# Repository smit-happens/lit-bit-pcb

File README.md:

# lit-bit-pcb
For the embedded systems lit-bit project

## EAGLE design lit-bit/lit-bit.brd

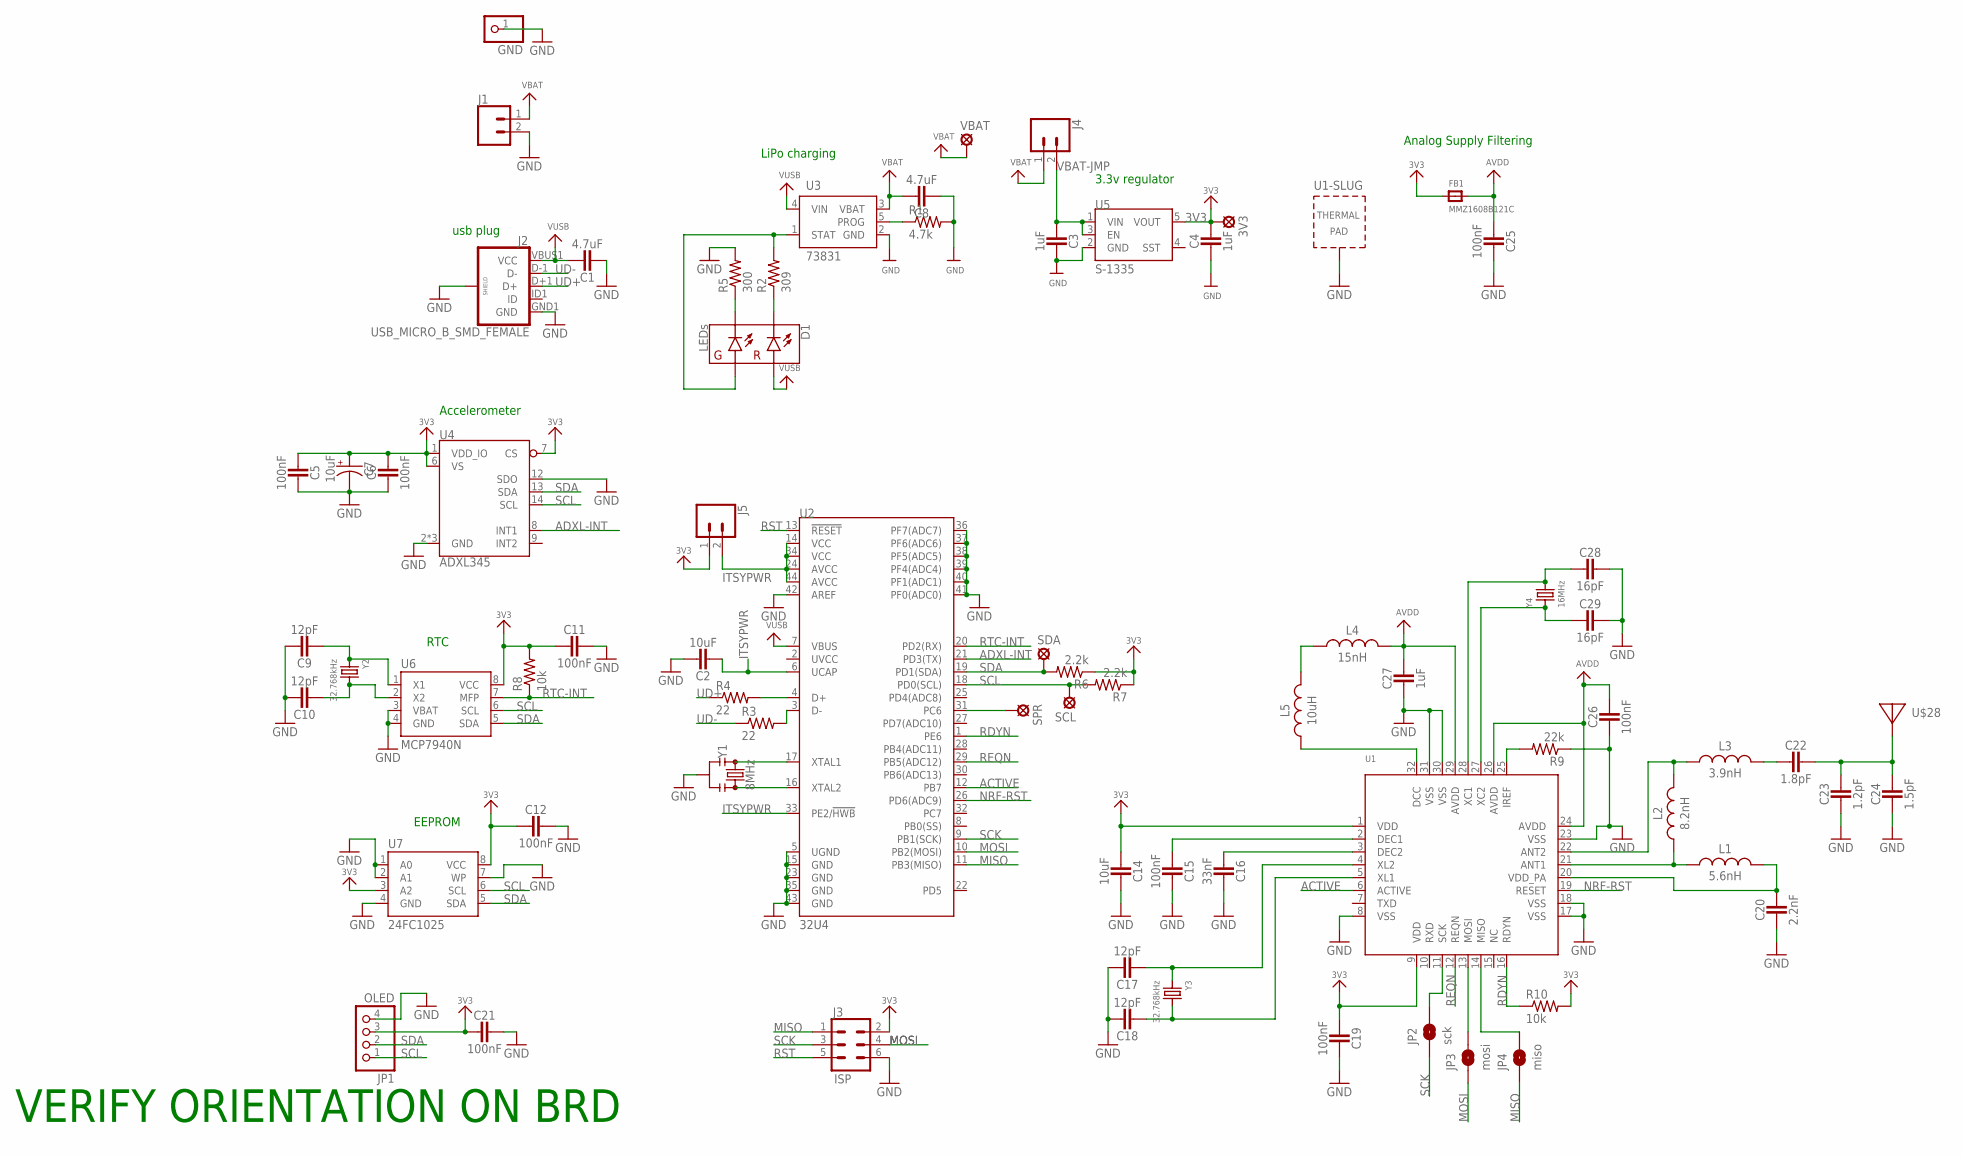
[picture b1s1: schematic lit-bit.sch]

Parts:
3V3: LSP10
C1, C8: 4.7uF; 0603
C2, C14: 10uF; 0603
C3, C4, C27: 1uF; 0603
C5, C6, C11, C12, C15, C19, C21, C25, C26: 100nF; 0603
C7: 10uF; 0805-POLAR
C9, C10, C17, C18: 12pF; 0603
C16: 33nF; 0603
C20: 2.2nF; 0603
C22: 1.8pF; 0603
C23: 1.2pF; 0603
C24: 1.5pF; 0603
C28, C29: 16pF; 0603
D1: LEDs; 0606
FB1: MMZ1608B121C; 0805
GND: HEADER-1X1ROUND; 1X01_ROUND
J1: CONN_02-JST-2MM-SMT; JST-2-SMD
J2: USB_MICRO_B_SMD_FEMALE; USB-B-MICRO-SMD
J3: ISP; 2X3
J4, J5: CONN_02; 1X02
JP1: OLED; 1X04_ROUND
JP2: sck; SMT-JUMPER_2_NO_SILK
JP3: mosi; SMT-JUMPER_2_NO_SILK
JP4: miso; SMT-JUMPER_2_NO_SILK
L1: 5.6nH; 0603
L2: 8.2nH; 0603
L3: 3.9nH; 0603
L4: 15nH; 0603
L5: 10uH; 0603
R1: 4.7k; 0603
R2: 309; 0603
R3, R4: 22; 0603
R5: 300; 0603
R6, R7: 2.2k; 0603
R8, R10: 10k; 0603
R9: 22k; 0603
SCL: LSP10
SDA: LSP10
SPR: LSP10
U1: NRF8001; QFN32_5MM
U2: 32U4; TQFP44
U3: 73831; SOT23-5
U4: ADXL345; LGA-14
U5: S-1335; SOT23-5
U6: MCP7940N; 8-SOIC_HAND_SOLDER
U7: 24FC1025; 8-SOIC_HAND_SOLDER
U$28: ANTENNA_PCBNRF8001_1.6MM; ANT_PCB_2.4GHZ_NRF8001_1.6MM_1OZ
VBAT: LSP10
Y1: 8MHz; RESONATOR-SMD-3.2X1.3
Y2, Y3: 32.768kHz; CRYSTAL_8X3.8
Y4: 16MHz; CRYSTAL_3.2X2.5

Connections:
3V3: 3V3.MP, C4.1, C5.2, C6.1, C7.1 (+), C11.2, C12.2, C14.2, C19.2, C21.2, FB1.1, J3.2, J5.1, JP1.3, R6.1, R7.1, R8.2, R10.2, U1.1 (VDD), U1.9 (VDD), U4.1 (VDD_IO), U4.6 (VS), U4.7 (CS), U5.5 (VOUT), U6.8 (VCC), U7.3 (A2), U7.8 (VCC)
ACTIVE: U1.6 (ACTIVE), U2.12 (PB7)
ADXL-INT: U2.21 (PD3(TX)), U4.8 (INT1)
AVDD: C25.2, C26.1, C27.1, FB1.2, L4.2, U1.24 (AVDD), U1.26 (AVDD), U1.29 (AVDD)
D+: R4.2, U2.4 (D+)
GND: C1.2, C2.1, C3.1, C4.2, C5.1, C6.2, C7.2 (-), C8.2, C9.1, C10.1, C11.1, C12.1, C14.1, C15.1, C16.1, C17.1, C18.1, C19.1, C20.2, C21.1, C23.2, C24.2, C25.1, C26.2, C27.2, C28.1, C29.1, GND.1, J1.2 (1), J2.GND1 (GND), J2.P$1 (SHIELD), J2.P$3 (SHIELD), J2.P$4 (SHIELD), J2.P$5 (SHIELD), J3.6, JP1.4, R1.2, R5.2, R9.1, U1.8 (VSS), U1.17 (VSS), U1.18 (VSS), U1.23 (VSS), U1.30 (VSS), U1.31 (VSS), U1.33 (TP), U2.5 (UGND), U2.15 (GND), U2.23 (GND), U2.35 (GND), U2.36 (PF7(ADC7)), U2.37 (PF6(ADC6)), U2.38 (PF5(ADC5)), U2.39 (PF4(ADC4)), U2.40 (PF1(ADC1)), U2.41 (PF0(ADC0)), U2.42 (AREF), U2.43 (GND), U3.2 (GND), U4.2 (GND), U4.4 (GND), U4.5 (GND), U4.12 (SDO), U5.2 (GND), U6.3 (VBAT), U6.4 (GND), U7.1 (A0), U7.2 (A1), U7.4 (GND), U7.7 (WP), Y1.2
ITSYPWR: C2.2, J5.2, U2.6 (UCAP), U2.14 (VCC), U2.24 (AVCC), U2.33 (PE2/!HWB), U2.34 (VCC), U2.44 (AVCC)
MISO: J3.1, JP4.1, U2.11 (PB3(MISO))
MOSI: J3.4, JP3.1, U2.10 (PB2(MOSI))
unnamed: U2.17 (XTAL1), Y1.1
unnamed: R1.1, U3.5 (PROG)
unnamed: D1.P$3 (GA), R2.2, U3.1 (STAT)
unnamed: D1.P$2 (RC), R2.1
unnamed: D1.P$4 (GC), R5.1
unnamed: R3.2, U2.3 (D-)
unnamed: U2.16 (XTAL2), Y1.3
unnamed: SPR.MP, U2.31 (PC6)
unnamed: C17.2, U1.4 (XL2), Y3.P$1 (1)
unnamed: C15.2, U1.2 (DEC1)
unnamed: C9.2, U6.1 (X1), Y2.P$1 (1)
unnamed: C10.2, U6.2 (X2), Y2.P$4 (2)
unnamed: C16.2, U1.3 (DEC2)
unnamed: C18.2, U1.5 (XL1), Y3.P$4 (2)
unnamed: C20.1, L1.2, U1.20 (VDD_PA)
unnamed: L1.1, L2.1, U1.21 (ANT1)
unnamed: JP2.2, U1.11 (SCK)
unnamed: L2.2, L3.1, U1.22 (ANT2)
unnamed: JP3.2, U1.13 (MOSI)
unnamed: R9.2, U1.25 (IREF)
unnamed: C22.2, L3.2
unnamed: C22.1, C23.1, C24.1, U$28.FEED
unnamed: C28.2, U1.28 (XC1), Y4.2
unnamed: JP4.2, U1.14 (MISO)
unnamed: L4.1, L5.2
unnamed: L5.1, U1.32 (DCC)
unnamed: C29.2, U1.27 (XC2), Y4.1
NRF-RST: U1.19 (RESET), U2.26 (PD6(ADC9))
RDYN: R10.1, U1.16 (RDYN), U2.1 (PE6)
REQN: U1.12 (REQN), U2.29 (PB5(ADC12))
RST: J3.5, U2.13 (!RESET)
RTC-INT: R8.1, U2.20 (PD2(RX)), U6.7 (MFP)
SCK: J3.3, JP2.1, U2.9 (PB1(SCK))
SCL: JP1.1, R7.2, SCL.MP, U2.18 (PD0(SCL)), U4.14 (SCL), U6.6 (SCL), U7.6 (SCL)
SDA: JP1.2, R6.2, SDA.MP, U2.19 (PD1(SDA)), U4.13 (SDA), U6.5 (SDA), U7.5 (SDA)
UD+: J2.D+1 (D+), R4.1
UD-: J2.D-1 (D-), R3.1
VBAT: C8.1, J1.1 (2), J4.1, U3.3 (VBAT), VBAT.MP
VBAT-JMP: C3.2, J4.2, U5.1 (VIN), U5.3 (EN)
VUSB: C1.1, D1.P$1 (RA), J2.VBUS1 (VCC), U2.7 (VBUS), U3.4 (VIN)

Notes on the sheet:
usb plug
LiPo charging
3.3v regulator
RTC
Accelerometer
EEPROM
VERIFY ORIENTATION ON BRD
Analog Supply Filtering

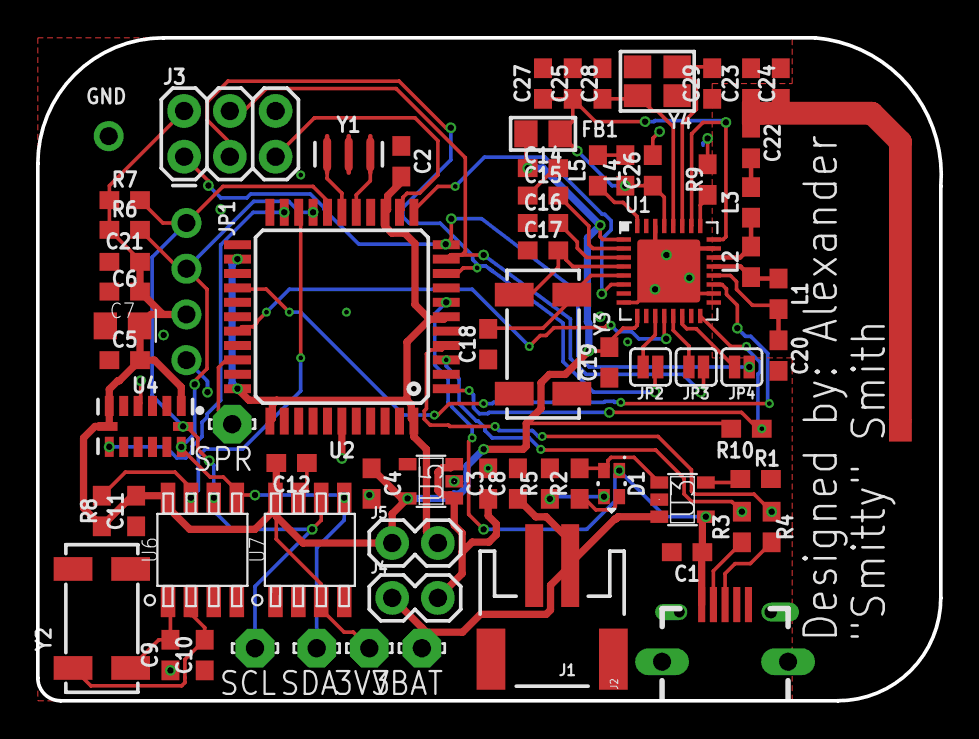
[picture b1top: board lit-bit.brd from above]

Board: 2 copper layers, 50.2 x 36.8 mm, 72 parts (0 on the bottom side), 49 nets.

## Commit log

2018-06-18 imported SCADA library and started project with 32u4
2018-06-19 added power circuitry
2018-06-19 imported TQFN package for 32u4
2018-06-19 removed QFN 32u4
2018-06-20 Added all the major components to sch working on BLE antenna
2018-06-20 finished the schematic starting on the brd now
2018-06-20 working through pcb placement
2018-06-20 finally laid out the board
2018-06-20 acktually done with layout now, got board dimensions
2018-06-20 laid out ground planes
2018-06-20 almost routed, but not working
2018-06-20 reworking
2018-06-20 routed the bluetooth module successfully
2018-06-21 fukky routed, but is ugly
2018-06-21 rotated the nrf module, having better luck but is still bad
2018-06-21 finally have something decent
2018-06-22 added gnd point for testing

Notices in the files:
parts and their libraries:
SparkFun-Connectors: Licensing: Creative Commons ShareAlike 4.0 International - https://creativecommons.org/licenses/by-sa/4.0
microbuilder: This work is placed in the public domain, and may be freely used for commercial and non-commercial work with the following conditions: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
